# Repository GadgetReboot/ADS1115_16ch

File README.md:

# ADS1115_16ch
<br><br><BR><BR>
Four ADS1115 16 bit ADCs on one pcb for up to 16 channels on a single I2C bus

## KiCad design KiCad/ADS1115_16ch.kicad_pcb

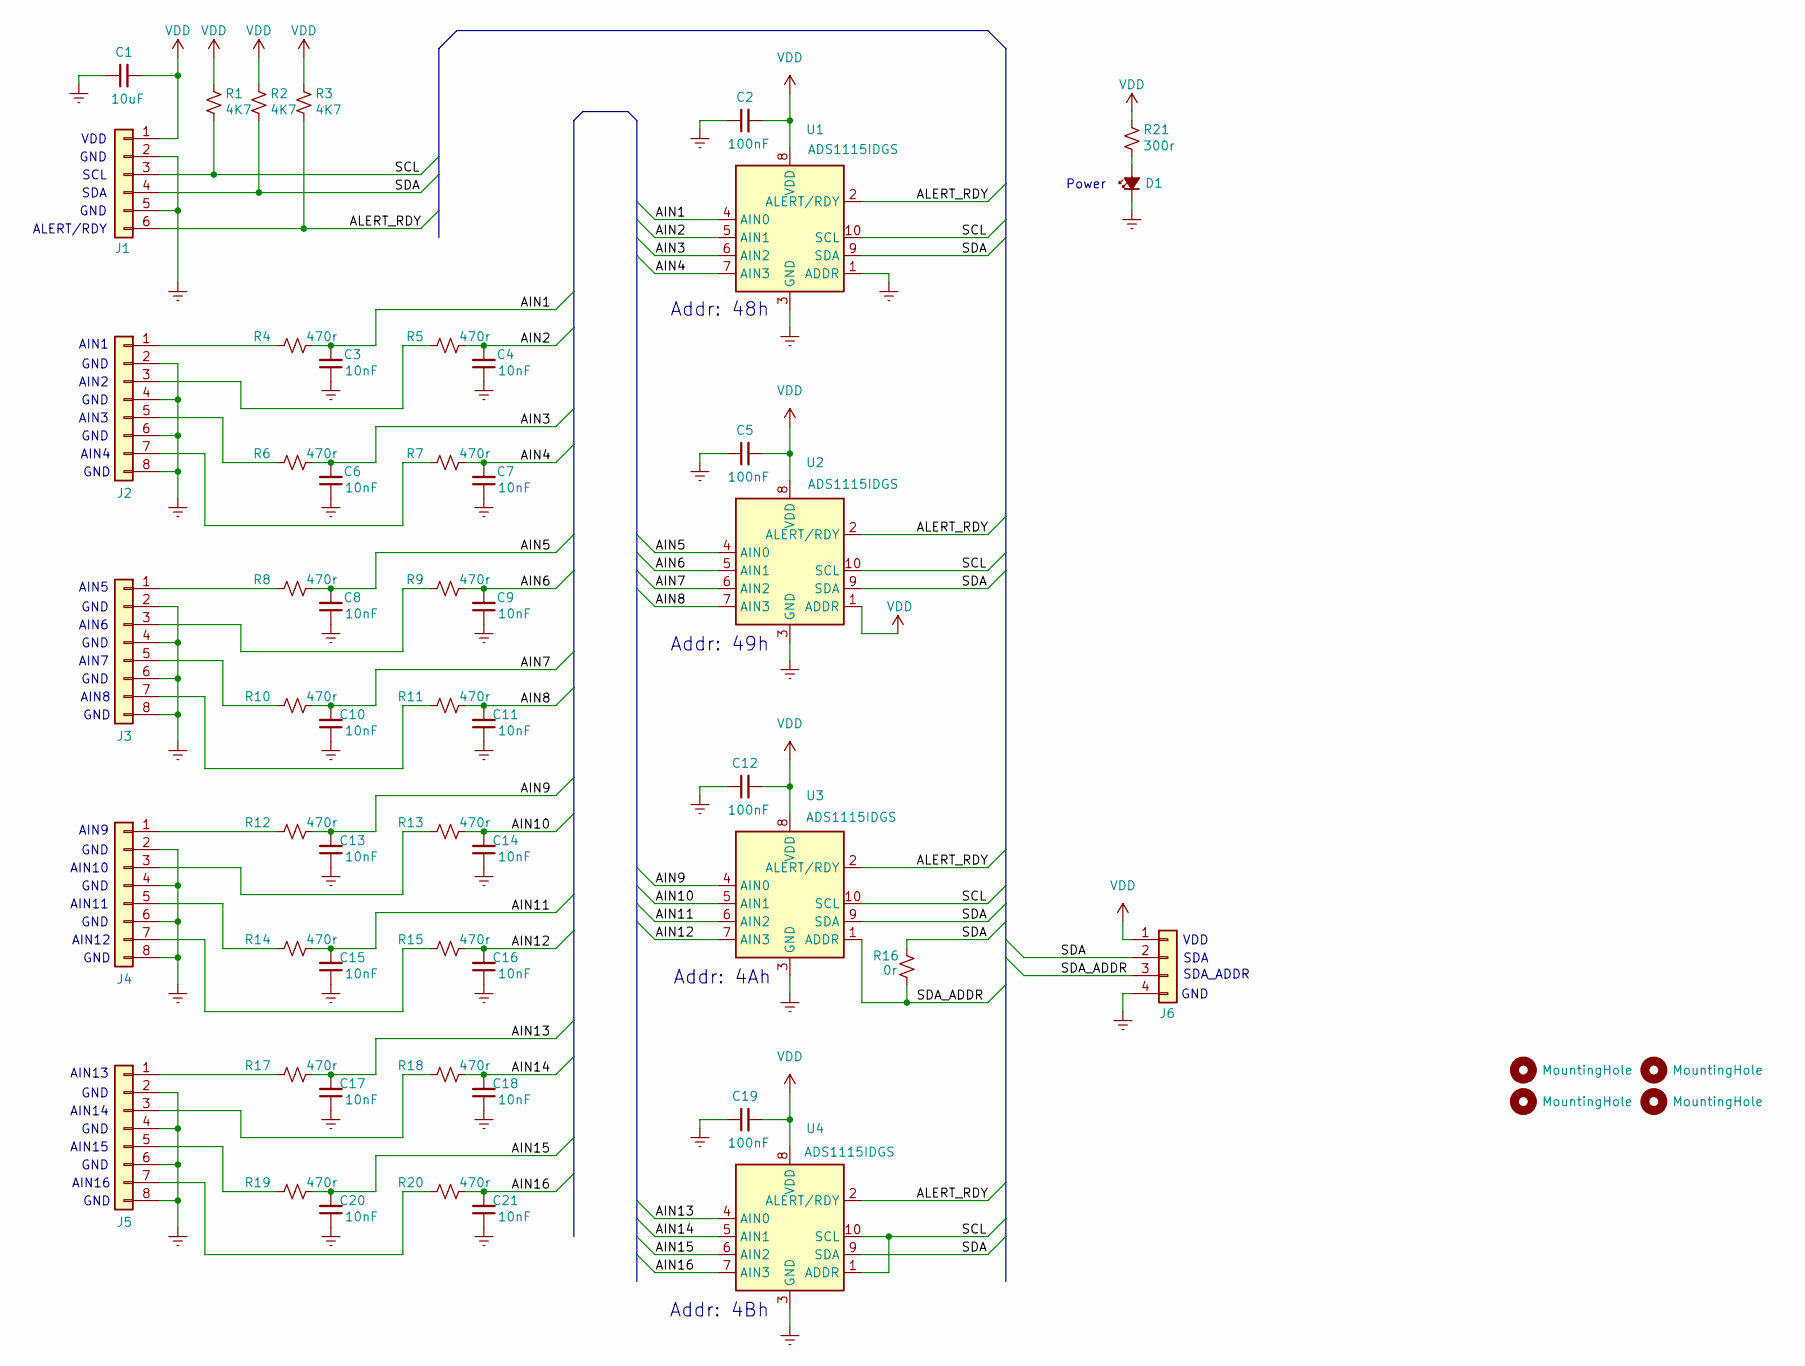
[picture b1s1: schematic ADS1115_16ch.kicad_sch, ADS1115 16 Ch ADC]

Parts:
C1: 10uF; C_0805_2012Metric_Pad1.18x1.45mm_HandSolder
C2, C5, C12, C19: 100nF; C_0805_2012Metric_Pad1.18x1.45mm_HandSolder
C3, C4, C6, C7, C8, C9, C10, C11, C13, C14, C15, C16, C17, C18, C20, C21: 10nF; C_0805_2012Metric_Pad1.18x1.45mm_HandSolder
D1: LED_Small_Filled; LED_0805_2012Metric_Pad1.15x1.40mm_HandSolder
H1, H2, H3, H4: MountingHole; MountingHole_3.5mm
J1: Conn_01x06; PinHeader_1x06_P2.54mm_Vertical
J2, J3, J4, J5: Conn_01x08; PinHeader_1x08_P2.54mm_Vertical
J6: Conn_01x04; PinHeader_1x04_P2.54mm_Vertical
R1, R2, R3: 4K7; R_0805_2012Metric_Pad1.20x1.40mm_HandSolder
R4, R5, R6, R7, R8, R9, R10, R11, R12, R13, R14, R15, R17, R18, R19, R20: 470r; R_0805_2012Metric_Pad1.20x1.40mm_HandSolder
R16: 0r; R_0805_2012Metric_Pad1.20x1.40mm_HandSolder
R21: 300r; R_0805_2012Metric_Pad1.20x1.40mm_HandSolder
U1, U2, U3, U4: ADS1115IDGS; TSSOP-10_3x3mm_P0.5mm

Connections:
/AIN1: C3.2, R4.2, U1.4 (AIN0)
/AIN2: C4.2, R5.2, U1.5 (AIN1)
/AIN3: C6.2, R6.2, U1.6 (AIN2)
/AIN4: C7.2, R7.2, U1.7 (AIN3)
/AIN5: C8.2, R8.2, U2.4 (AIN0)
/AIN6: C9.2, R9.2, U2.5 (AIN1)
/AIN7: C10.2, R10.2, U2.6 (AIN2)
/AIN8: C11.2, R11.2, U2.7 (AIN3)
/AIN9: C13.2, R12.2, U3.4 (AIN0)
/AIN10: C14.2, R13.2, U3.5 (AIN1)
/AIN11: C15.2, R14.2, U3.6 (AIN2)
/AIN12: C16.2, R15.2, U3.7 (AIN3)
/AIN13: C17.2, R17.2, U4.4 (AIN0)
/AIN14: C18.2, R18.2, U4.5 (AIN1)
/AIN15: C20.2, R19.2, U4.6 (AIN2)
/AIN16: C21.2, R20.2, U4.7 (AIN3)
/ALERT_RDY: J1.6, R3.2, U1.2 (ALERT/RDY), U2.2 (ALERT/RDY), U3.2 (ALERT/RDY), U4.2 (ALERT/RDY)
/SCL: J1.3, R1.2, U1.10 (SCL), U2.10 (SCL), U3.10 (SCL), U4.1 (ADDR), U4.10 (SCL)
/SDA: J1.4, J6.2, R2.2, R16.2, U1.9 (SDA), U2.9 (SDA), U3.9 (SDA), U4.9 (SDA)
/SDA_ADDR: J6.3, R16.1, U3.1 (ADDR)
GNDREF: C1.1, C2.1, C3.1, C4.1, C5.1, C6.1, C7.1, C8.1, C9.1, C10.1, C11.1, C12.1, C13.1, C14.1, C15.1, C16.1, C17.1, C18.1, C19.1, C20.1, C21.1, D1.1 (K), J1.2, J1.5, J2.2, J2.4, J2.6, J2.8, J3.2, J3.4, J3.6, J3.8, J4.2, J4.4, J4.6, J4.8, J5.2, J5.4, J5.6, J5.8, J6.4, U1.1 (ADDR), U1.3 (GND), U2.3 (GND), U3.3 (GND), U4.3 (GND)
unnamed: D1.2 (A), R21.2
unnamed: J2.1, R4.1
unnamed: J2.3, R5.1
unnamed: J2.5, R6.1
unnamed: J2.7, R7.1
unnamed: J3.1, R8.1
unnamed: J3.3, R9.1
unnamed: J3.5, R10.1
unnamed: J3.7, R11.1
unnamed: J4.1, R12.1
unnamed: J4.3, R13.1
unnamed: J4.5, R14.1
unnamed: J4.7, R15.1
unnamed: J5.1, R17.1
unnamed: J5.3, R18.1
unnamed: J5.5, R19.1
unnamed: J5.7, R20.1
VDD: C1.2, C2.2, C5.2, C12.2, C19.2, J1.1, J6.1, R1.1, R2.1, R3.1, R21.1, U1.8 (VDD), U2.1 (ADDR), U2.8 (VDD), U3.8 (VDD), U4.8 (VDD)

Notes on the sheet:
GND
AIN14
AIN7
SDA_ADDR
SCL
AIN13
AIN11
Addr: 4Bh
AIN3
Addr: 48h
Addr: 49h
ALERT/RDY
AIN15
AIN10
AIN8
AIN16
AIN4
VDD
AIN9
AIN6
AIN2
Power
Addr: 4Ah
AIN12
SDA
AIN1
AIN5

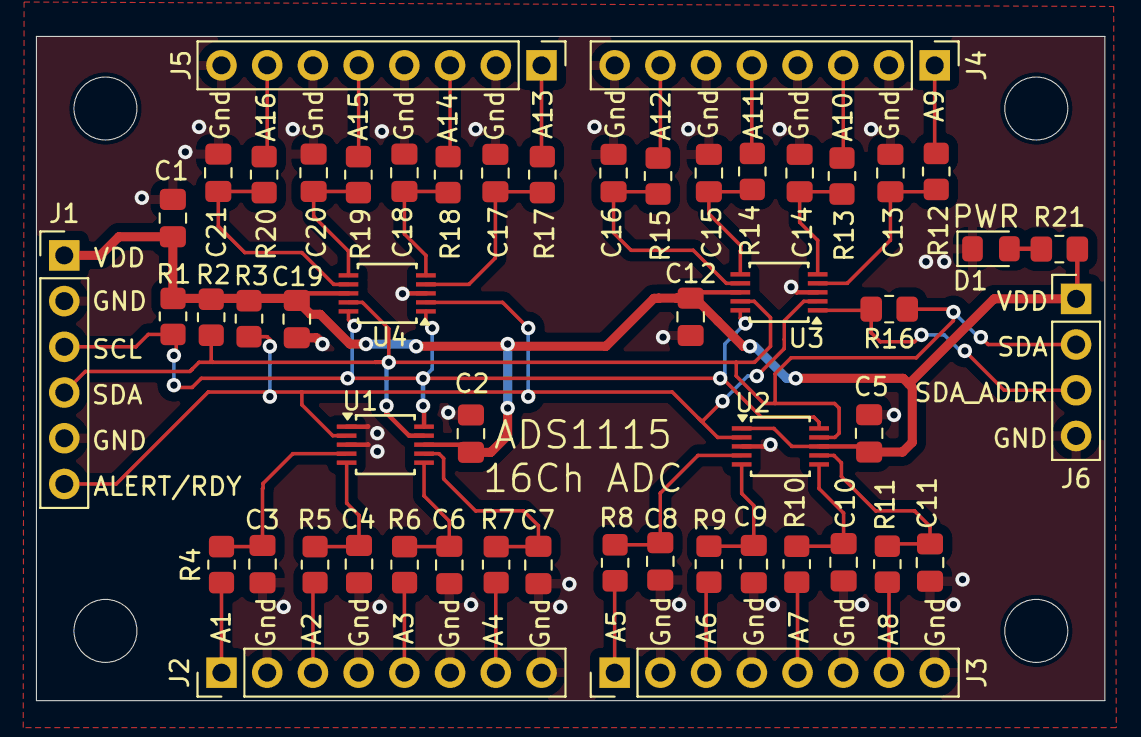
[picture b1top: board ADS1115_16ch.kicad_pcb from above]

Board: 2 copper layers, 59.4 x 36.9 mm, 57 parts (0 on the bottom side), 39 nets.
